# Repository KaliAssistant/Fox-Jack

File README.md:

# Fox-Jack
> Portable social-engineering LAN tool for automated payloads and wired audits — based on Luckfox Pico Max

## About

**Fox-Jack** is a low-cost, DIY social engineering LAN implant inspired by the Hak5 SharkJack.  
Designed for payload delivery, opportunistic wired auditing, and SE engagements, it features DIP-switch mode control, RGB LED feedback, and USB gadget interfaces — all powered by the **Luckfox Pico Max (RV1106G3)**.

### Features

* USB gadget function: **RNDIS** over USB
* 100 Mbps onboard **GMAC** Ethernet
* Based on **Luckfox Pico Max (RV1106G3)**
* Optional **open-source extension board PCB**:

  * 300mAh LiPo battery support (\~1–2hr uptime, longer with bigger battery)
  * **NeoPixel RGB LED** status indicator
  * **2-position DIP switch** to select payloads
* Optional **3D printable cases**
* Rootfs: **Buildroot**
* Boot: **SD card**
* U-Boot: **Luckfox official SDK**

---

## Repository Contents

* 🧰 **Luckfox Pico Official SDK**
* 🔨 **Image build scripts**
* 🧱 **3D-printable case designs**
* 🗒 **Optional extension board**:

  * KiCad project
  * Gerber files
  * BOM

---

## Parts List

| Item                                       | Qty | Link |
| ------------------------------------------ | --- | ---- |
| Luckfox Pico MAX (256 MB RAM version only) | 1   | [Amazon](https://a.co/d/7qTUaEF) |
| M2x0.4 Heat-Set Thread Insert (D3×H2.5)    | 2   | [Amazon](https://a.co/d/6mJeA5C) |
| M2x0.4 Heat-Set Thread Insert (D3×H2)      | 2   | [Amazon](https://a.co/d/6mJeA5C) |
| M2x0.4 Ultra-Low Head Torx Screws (3mm)    | 2   | [Amazon](https://a.co/d/fiHYJ7t) |
| M2x0.4 Hex Socket Head Cap Screws (10mm)   | 2   | [Amazon](https://a.co/d/4TCJOGo) |
| DIP Switch 1 Positions                     | 1   | [Amazon](https://a.co/d/8rEHPwg) |
| 302040 Lipo 3.7v battery                   | 1   | [Amazon](https://amzn.eu/d/auT4PZT) |

> [!NOTE]
> 🔧 PCB & BOM: all files in the `pcb/` directory

---

## Required Tools

* 28 AWG electrical wire
* Soldering tools:

  * Solder
  * Solder iron
  * Solder paste
  * Solder flux
  * Hot air gun (for SMD components on extension board)

---

## Fox-Jack EXT Board

#### Assembly Notes: [README](./pcb/README.md)

---

## 3D printable cases

#### see: [README](./3dp/README.md)

---

## Build Instructions

1. Create a Debian/Ubuntu/Kali (or other Debian-based) Linux environment
   *(You can use a VM or physical machine — author uses a Debian laptop)*

2. Install required dependencies:

   ```bash
   sudo ./dep.sh
   sudo apt update
   sudo apt install -y docker.io kconfig-frontends make cmake automake autoconf libtool libtool-bin rsync
   ```
   
3. Clone the repository:

   ```bash
   git clone https://github.com/KaliAssistant/Fox-Jack.git
   ```

4. Navigate into the repo:

   ```bash
   cd Fox-Jack
   ```

5. Run the build script:

   ```bash
   sudo ./build.sh all
   ```

   You will see the SDK's *lunch menu*:

   ```
   You're building on Linux
   Lunch menu...pick the Luckfox Pico hardware version:
   [4] RV1106_Luckfox_Pico_Pro_Max
   ...
   Which would you like? [default: 0]: 4

   Lunch menu...pick the boot medium:
   [0] SD_CARD
   Which would you like? [default: 0]: 0

   Lunch menu...pick the system version:
   [0] Buildroot
   Which would you like? [default: 0]: 0
   ```

> [!NOTE]
> ✅ Just enter `4 / 0 / 0` — **only Luckfox Pico Max** is supported currently.

---

## Config Options

You can tweak build options using the following:

* **Buildroot menuconfig**:

  ```bash
  sudo ./build.sh luckfox buildrootconfig
  ```

* **Kernel menuconfig**:

  ```bash
  sudo ./build.sh luckfox kernelconfig
  ```

* **Foxjack extra config (e.g., SSH key, services)**:

  ```bash
  sudo ./build.sh foxjackconfig
  ```

> [!NOTE]
> **Security Note:**
> Default root password is `foxjack`, but **SSH password login is disabled** (`PermitRootLogin prohibit-password`) for security.
> Add your public key via `foxjackconfig`.
> If you need password login, modify `/etc/ssh/sshd_config` in rootfs manually.

To access via **USB RNDIS**, make sure your host PC has a static IP in the same subnet as defined in `foxjackconfig`.

---

## Flashing to SD Card

Once the build is complete, flash the image:

```bash
sudo ./build.sh sdflash
```

You'll see:

```
WARNING: Check the SD card dev path! blkenvflash can overwrite your system drives!
Enter your SD card dev path (/dev/sxx)... >
```

> [!WARNING]
> **Be careful!** Enter the correct SD card device path to avoid overwriting your OS drive.

---

## Run Modes (Payload Selection)

Fox-Jack supports 4 modes, selected via a 2-position DIP switch:

| Mode      | SW1 | SW2 | Description    |
| --------- | --- | --- | -------------- |
| 0 (debug) | 0   | 0   | Dev/debug mode |
| 1         | 1   | 0   | Payload 1      |
| 2         | 0   | 1   | Payload 2      |
| 3         | 1   | 1   | Payload 3      |

Read via GPIO:

```c
#define SW1_PIN 67  // gpio2_a3_d (pin 27)
#define SW2_PIN 66  // gpio2_a2_d (pin 26)
```

---

### Debug Mode Details

In **debug mode** (SW1=0, SW2=0):

* USB gadget provides **RNDIS Ethernet** **+ Mass Storage**
* Payloads can be edited directly from host PC
* **LOOT** (results, passwords, hashes) is saved in:

  ```
  <UMS>/loot/
  ```

---

## Payload Examples

#### see [README](./payload_examples/README.md)

Payload filenames must follow this format:

```
E????-name.payload
```

* `E????` is a 4-digit payload ID (e.g., `E0000`)
* `name` is a short, descriptive label

**Example:**

```
E0000-arp-scan.payload
```

---

## Disclaimer

**Fox-Jack** is intended for authorized security testing, educational, and research purposes only.  
Use of this device without explicit permission on networks or systems you do not own or have authorization to test is illegal and unethical.  
The author and contributors are not responsible for any misuse or damage caused by this tool.  
Please ensure you comply with all applicable laws and obtain proper consent before deployment.

---

## License

Fox-Jack is open-source and released under the **GNU General Public License v3.0 (GPLv3)**.
You are free to use, modify, and redistribute under the terms of this license.

See the [`LICENSE`](./LICENSE) file for full details.

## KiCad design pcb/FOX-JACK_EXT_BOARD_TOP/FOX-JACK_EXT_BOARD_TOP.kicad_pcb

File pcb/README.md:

# FOX-JACK\_EXT\_BOARD

This directory contains the open-source **extension board** for the [Fox-Jack](https://github.com/KaliAssistant/Fox-Jack) project.

Designed with a **stacked PCB layout** inspired by modular smartphones (like iPhones), the board achieves a **compact**, **robust**, and **DIY-friendly** assembly with the **Luckfox Pico Max**.

---

## Board Structure

The extension board is made up of **two stacked PCBs**:

### 1. `FOX-JACK_EXT_BOARD_TOP`

* Primary functional PCB
* PCB thickness: **0.8mm**
* Hosts core components: battery management, WS2812 (NeoPixel), DIP switch, etc.

### 2. `FOX-JACK_EXT_BOARD_MID`

* Acts as a **mechanical connector** and **base shim**
* PCB thickness: **1.6mm**
* Designed to fit perfectly between the `TOP` board and the **Luckfox Pico Max**
* Provides mechanical rigidity and solder alignment

> [!NOTE]
>  This stacked layout allows professional-looking compact integration at minimal cost and effort.

---

## Assembly Notes

> [!NOTE]
> Soldering requires careful thermal profiling!

* **Top Board (`TOP`)**

  * Use **high-temperature solder paste** (e.g., Sn63/Pb37 or SAC305)

* **Mid Board (`MID`)**

  * Use **low-temperature solder paste** (e.g., Sn42/Bi58) for the mechanical + electrical bridge with the Pico board
  * Helps avoid reflowing the `TOP` board during final reflow

---

## Battery Info

* Recommended: **Li-ion 3.7V 300mAh**
* Model: **302040**
* Chosen to fit snugly inside the 3D-printed case in this repo

---

## ADC Voltage Measurement

If you want to **read battery voltage** using the **Pico’s ADC**:

* Remove **R57** on the **Luckfox Pico Max PCB**
* (R57 is a **10K ±5% pull-up** resistor that affects accurate voltage reading)
* See https://github.com/LuckfoxTECH/luckfox-pico/issues/174

---

## Compatibility with 3D-Printed Case

To fit the extension + Pico board into the provided **3D-printed case**, perform the following hardware mods:

1. **Remove** the following components from the Pico:

   * **RJ45 Ethernet socket**
   * **CSI Camera connector**
   * **RTC battery holder**

2. **Modify Ethernet Cable**:

   * Cut and strip a short **4P (or 8P)** RJ45 cable
   * Remove filler and outer jacket
   * Solder directly to the Pico’s Ethernet pads
   * 4P is enough for **100 Mbps** **(rv1106g3 gmac only support 100Mbps phy)**

---

## Files Included

* ✅ KiCad project files (`.kicad_pcb`, `.sch`, etc.)
* ✅ Gerber + drill files (for fabrication)
* ✅ BOM (Bill of Materials)
* ✅ Assembly guidelines
* ✅ 3D models and printable case (`.stl`, in [<repo_dir>/3dp](../3dp/))

---

## PCB Manufacturing Notes (e.g., JLCPCB)

When ordering:

* ✅ Use **standard PCB processing** (no special options)
* ❗️ **Do NOT enable “Castellated Holes”** — leave this option **unchecked**
* ✅ This keeps the board cost around **\$4 USD**
* ❌ Enabling Castellated Holes may raise the quote to **\$40+ USD**, unnecessarily

> [!NOTE]
> This design **does not use true castellated holes**.
> Instead, it relies on **DIY-style side solder bridging** using exposed edge pads on a regular PCB.
> This approach is **cost-efficient**, **strong enough**, and perfectly suited for **DIY assembly** — no need for expensive edge plating.

---

## License

Licensed under **GNU GPLv3**.
Feel free to **use**, **study**, **modify**, and **share** under the same license.

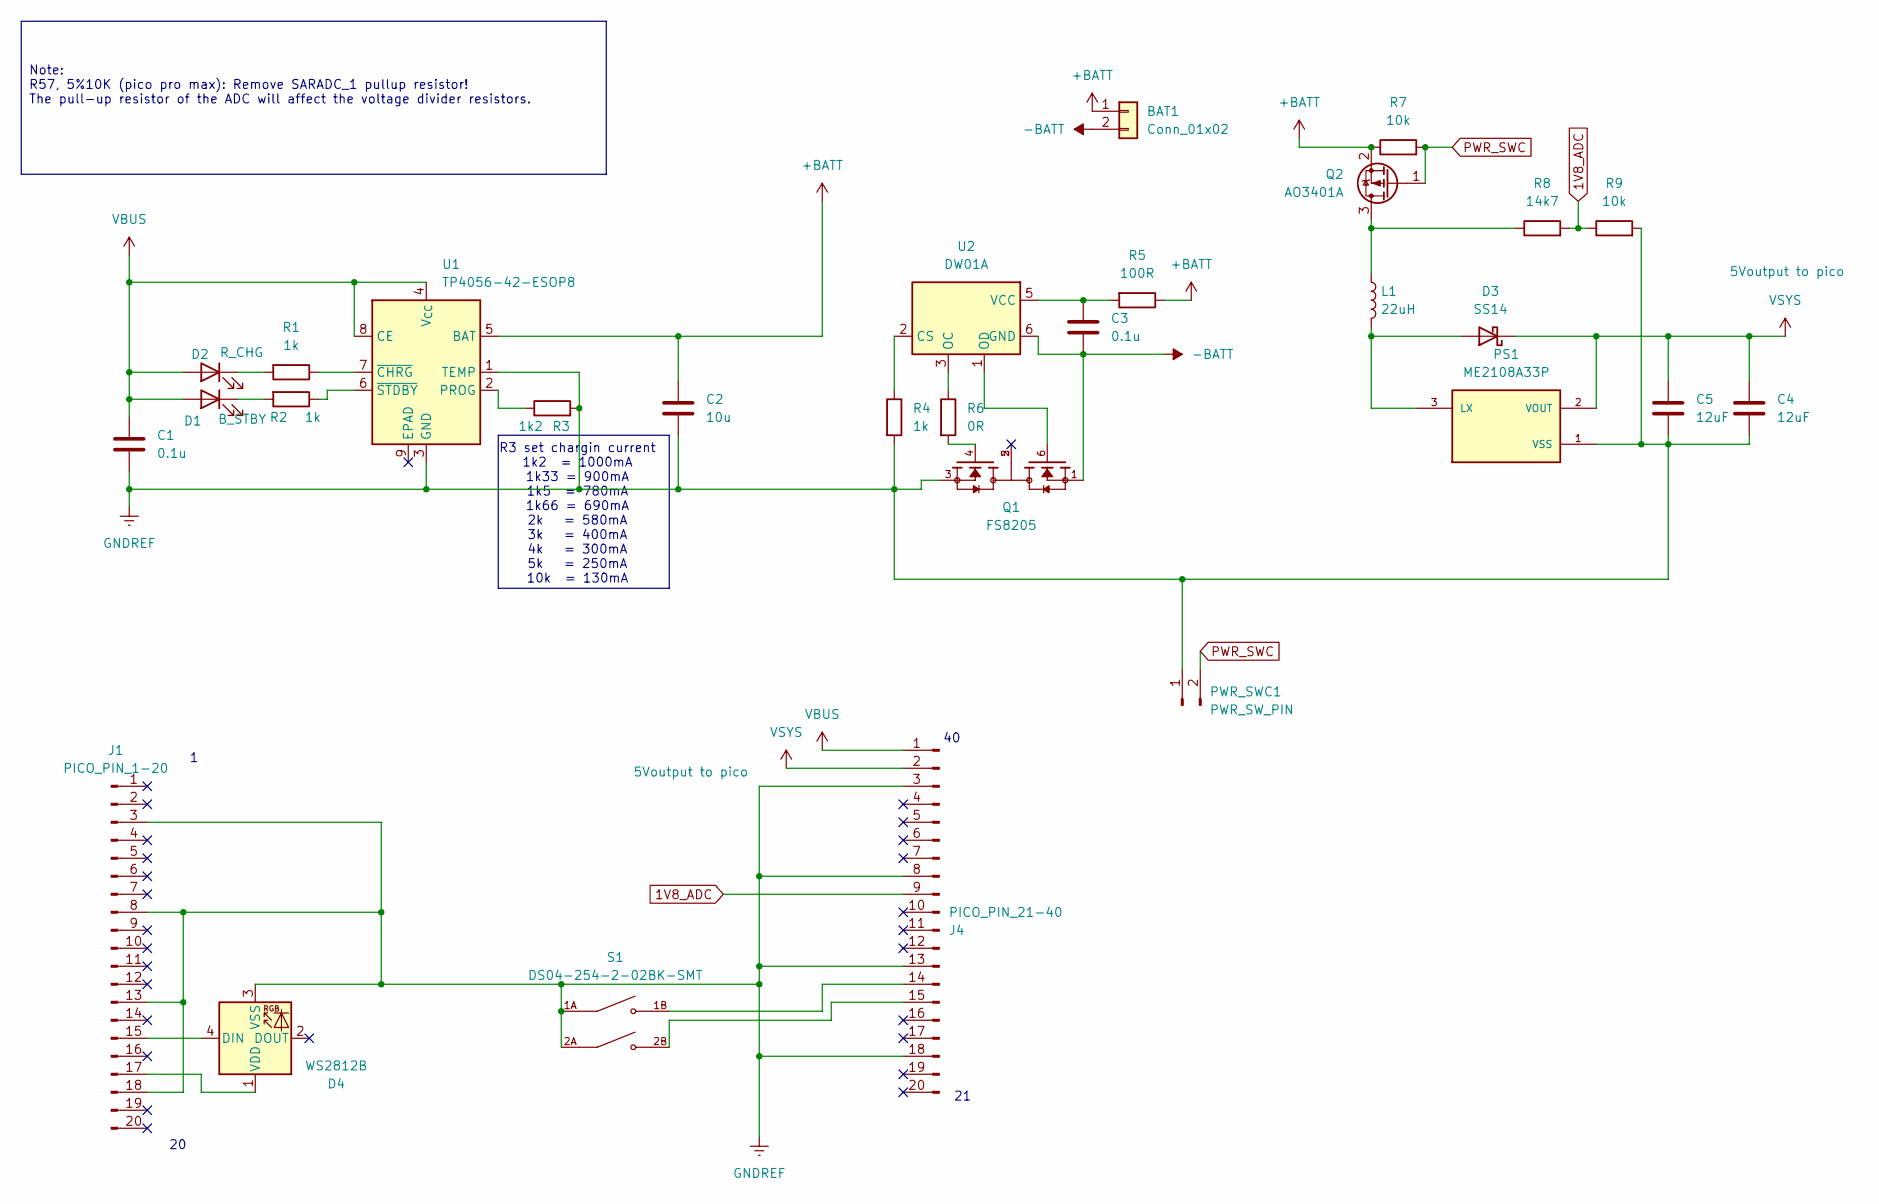
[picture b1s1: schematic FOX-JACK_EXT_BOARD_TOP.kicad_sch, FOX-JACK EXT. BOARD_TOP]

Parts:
BAT1: Conn_01x02; BAT_PAD
C1, C3: 0.1u; C_0402_1005Metric
C2: 10u; C_0603_1608Metric
C4, C5: 12uF; C_1210_3225Metric
D1: B_STBY; LED_0603_1608Metric
D2: R_CHG; LED_0603_1608Metric
D3: SS14; D_SMA
D4: WS2812B; LED_WS2812B_PLCC4_5.0x5.0mm_P3.2mm
J1: PICO_PIN_1-20; PinHeader_1x20_P2.54mm_Vertical
J4: PICO_PIN_21-40; PinHeader_1x20_P2.54mm_Vertical
L1: 22uH; L_Changjiang_FNR3015S
PS1: ME2108A33P; CONV_ME2108A33P; PARTREV V10.0
PWR_SWC1: PWR_SW_PIN; PinHeader_1x02_P2.54mm_Vertical
Q1: FS8205; SOT95P280X145-6N; PARTREV 1.9
Q2: AO3401A; SOT-23
R1, R2: 1k; R_0402_1005Metric
R3: 1k2; LED_0402_1005Metric
R4: 1k; R_0603_1608Metric
R5: 100R; R_0805_2012Metric
R6: 0R; LED_0805_2012Metric
R7, R9: 10k; R_0402_1005Metric
R8: 14k7; R_0402_1005Metric
S1: DS04-254-2-02BK-SMT; SW_DS04-254-2-02BK-SMT; PARTREV V0.0
U1: TP4056-42-ESOP8; SOIC-8-1EP_3.9x4.9mm_P1.27mm_EP2.41x3.3mm_ThermalVias
U2: DW01A; SOT-23-6

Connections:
1V8_ADC: J4.9, R8.2, R9.1
+BATT: BAT1.1, C2.1, Q2.2 (S), R5.1, R7.1, U1.5 (BAT)
-BATT: BAT1.2, C3.2, Q1.1, U2.6 (GND)
GNDREF: C1.2, C2.2, C4.2, C5.2, D4.3 (VSS), J1.3, J1.8, J1.13, J1.18, J4.3, J4.8, J4.13, J4.18, PS1.1 (VSS), PWR_SWC1.1, Q1.3, R3.2, R4.2, R9.2, S1.1A, S1.2A, U1.1 (TEMP), U1.3 (GND)
unnamed: D1.1 (K), R2.2
unnamed: D2.1 (K), R1.2
unnamed: D3.2 (A), L1.2, PS1.3 (LX)
unnamed: D4.4 (DIN), J1.15
unnamed: D4.1 (VDD), J1.17
unnamed: J4.14, S1.1B
unnamed: J4.15, S1.2B
unnamed: Q1.4, R6.2
unnamed: L1.1, Q2.3 (D), R8.1
unnamed: R3.1, U1.2 (PROG)
unnamed: R1.1, U1.7 (~CHRG)
unnamed: R2.1, U1.6 (~STDBY)
unnamed: R4.1, U2.2 (CS)
unnamed: R6.1, U2.3 (OC)
unnamed: Q1.6, U2.1 (OD)
unnamed: C3.1, R5.2, U2.5 (VCC)
PWR_SWC: PWR_SWC1.2, Q2.1 (G), R7.2
VBUS: C1.1, D1.2 (A), D2.2 (A), J4.1, U1.4 (V_{CC}), U1.8 (CE)
VSYS: C4.1, C5.1, D3.1 (K), J4.2, PS1.2 (VOUT)

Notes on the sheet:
R3 set chargin current 1k2 = 1000mA 1k33 = 900mA 1k5 = 780mA 1k66 = 690mA 2k = 580mA 3k = 400mA 4k = 300mA 5k = 250mA 10k = 130mA
Note: R57, 5%10K (pico pro max): Remove SARADC_1 pullup resistor! The pull-up resistor of the ADC will affect the voltage divider resistors.

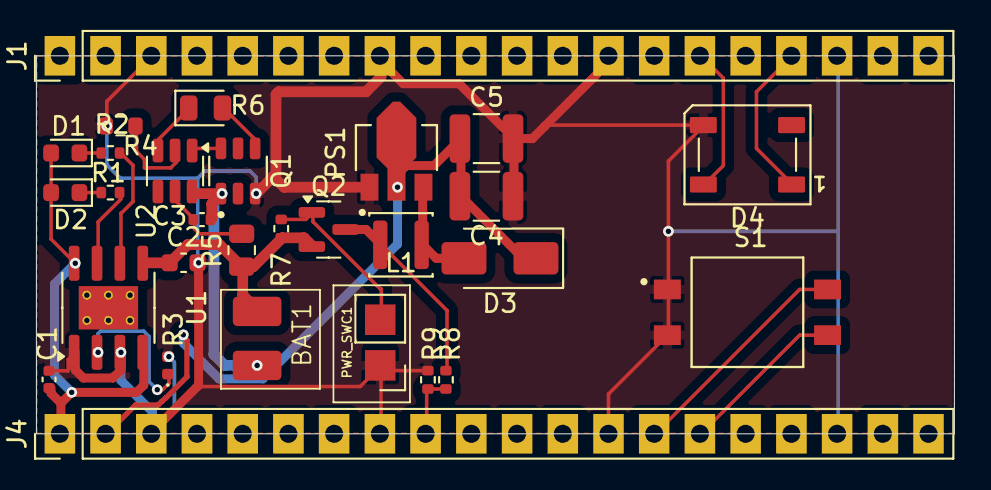
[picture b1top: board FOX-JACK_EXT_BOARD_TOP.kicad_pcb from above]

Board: 2 copper layers, 51.0 x 21.0 mm, 29 parts (0 on the bottom side), 23 nets.

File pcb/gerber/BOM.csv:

Index,LCSC#,MPN,Manufacturer,Package,Customer #,Description,RoHS,Quantity,MOQ,Multiple,Unit Price($),Extended Price($),Product Link
1,C236798,ME2108A50PG,MICRONE,SOT-89-3,PS1,Boost 5V 400mA 900mV~6.5V SOT-89-3 DC-DC Converters ROHS,yes,5,5,5,0.0680,0.34,https://lcsc.com/product-detail/dc-dc-converters_microne-me2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
2,C21190,0603WAF1001T5E,UNI-ROYAL,0603,R4,100mW Thick Film Resistor 75V ±100ppm/℃ ±1% 1kΩ 0603 Chip Resistor - Surface Mount ROHS,yes,100,100,100,0.0011,0.11,https://lcsc.com/product-detail/chip-resistor-surface-mount_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
3,C83852,SS14,onsemi,SMA(DO-214AC),D3,40V 500mV@1A 1A SMA(DO-214AC) Schottky Diodes ROHS,yes,5,5,5,0.1319,0.66,https://lcsc.com/product-detail/schottky-diodes_onsemi-ss14_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
4,C281774,RT0402BRD0714K7L,YAGEO,0402,R8,62.5mW Thin Film Resistor 50V ±25ppm/℃ ±0.1% 14.7kΩ 0402 Chip Resistor - Surface Mount ROHS,yes,50,50,50,0.0195,0.98,https://lcsc.com/product-detail/chip-resistor-surface-mount_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
5,C15127,AO3401A,AOS,SOT-23,Q2,"30V 85mΩ@2.5V,2.5A 1.3V@250uA 1 P-Channel SOT-23 MOSFETs ROHS",yes,10,10,10,0.0602,0.60,https://lcsc.com/product-detail/mosfets_aos-ao3401a_C15127.html
6,C19702,CL10A106KP8NNNC,Samsung Electro-Mechanics,0603,C2,10V 10uF X5R ±10% 0603 Multilayer Ceramic Capacitors MLCC - SMD/SMT ROHS,yes,20,20,20,0.0058,0.12,https://lcsc.com/product-detail/multilayer-ceramic-capacitor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
7,C60490,RC0402FR-0710KL,YAGEO,0402,"R7,R9",62.5mW Thick Film Resistor 50V ±100ppm/℃ ±1% 10kΩ 0402 Chip Resistor - Surface Mount ROHS,yes,100,100,100,0.0006,0.06,https://lcsc.com/product-detail/chip-resistor-surface-mount_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
8,C17477,0805W8F0000T5E,UNI-ROYAL,0805,R6,125mW Thick Film Resistor 150V ±800ppm/℃ ±1% 0Ω 0805 Chip Resistor - Surface Mount ROHS,yes,100,100,100,0.0017,0.17,https://lcsc.com/product-detail/chip-resistor-surface-mount_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
9,C2843785,XL-5050RGBC-WS2812B,XINGLIGHT,SMD5050,D4,SMD5050 RGB LEDs(Built-in IC) ROHS,yes,10,10,10,0.0490,0.49,https://lcsc.com/product-detail/rgb-leds-built-in-ic_xinglig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
10,C167761,FNR3015S220MT,cjiang (Changjiang Microelectronics Tech),"SMD,3x3mm",L1,"690mA 22uH Magnetic Shielded Inductor ±20% 680mA SMD,3x3mm Power Inductors ROHS",yes,20,20,20,0.0735,1.47,https://lcsc.com/product-detail/power-inductors_cjiang-chang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
11,C6331180,2.54-2P TPGT,SHOU HAN,SMD,S1,"2 SPST 24V Black 25mA 3,000 Cycles Slide, Rocked SMD DIP Switches ROHS",yes,1,1,1,0.4163,0.42,https://lcsc.com/product-detail/dip-switches_shou-han-2-54-2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
12,C60474,CC0402KRX7R7BB104,YAGEO,0402,"C1,C3",16V 100nF X7R ±10% 0402 Multilayer Ceramic Capacitors MLCC - SMD/SMT ROHS,yes,100,100,100,0.0009,0.09,https://lcsc.com/product-detail/multilayer-ceramic-capacitor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
13,C965799,XL-1608SURC-06,XINGLIGHT,0603,D2,20mA 225mcd Water Clear op View Mount 620nm~630nm Red 120° 50mW 2.3V 0603 LED Indication - Discrete ROHS,yes,100,100,100,0.0032,0.32,https://lcsc.com/product-detail/led-indication-discrete_xing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
14,C138687,CL32B106KBJNNNE,Samsung Electro-Mechanics,1210,"C4,C5",50V 10uF X7R ±10% 1210 Multilayer Ceramic Capacitors MLCC - SMD/SMT ROHS,yes,2,1,1,0.1571,0.31,https://lcsc.com/product-detail/multilayer-ceramic-capacitor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
15,C382139,TP4056,TPOWER,ESOP-8,U1,4V~6V Lithium-ion/Polymer 1 ESOP-8 Battery Management ROHS,yes,5,5,5,0.0888,0.44,https://lcsc.com/product-detail/battery-management_tpower-tp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
16,C17408,0805W8F1000T5E,UNI-ROYAL,0805,R5,125mW Thick Film Resistor 150V ±100ppm/℃ ±1% 100Ω 0805 Chip Resistor - Surface Mount ROHS,yes,100,100,100,0.0019,0.19,https://lcsc.com/product-detail/chip-resistor-surface-mount_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
17,C106235,RC0402FR-071KL,YAGEO,0402,"R1,R2",62.5mW Thick Film Resistor 50V ±100ppm/℃ ±1% 1kΩ 0402 Chip Resistor - Surface Mount ROHS,yes,100,100,100,0.0006,0.06,https://lcsc.com/product-detail/chip-resistor-surface-mount_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
18,C2927799,DW01A,YONGYUTAI,SOT-23-6,U2,1.5V~8V Lithium-ion/Polymer 1 SOT-23-6 Battery Management ROHS,yes,20,20,20,0.0247,0.49,https://lcsc.com/product-detail/battery-management_yongyutai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
19,C965807,XL-1608UBC-04,XINGLIGHT,0603,D1,20mA 300mcd Water Clear op View Mount 455nm~475nm Blue 120° 70mW 3.3V 0603 LED Indication - Discrete ROHS,yes,100,100,100,0.0035,0.35,https://lcsc.com/product-detail/led-indication-discrete_xing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
20,C2909307,FRC0402F1201TS,FOJAN,0402,R3,62.5mW Thick Film Resistor 50V ±100ppm/℃ ±1% 1.2kΩ 0402 Chip Resistor - Surface Mount ROHS,yes,100,100,100,0.0005,0.05,https://lcsc.com/product-detail/chip-resistor-surface-mount_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
21,C2830320,FS8205A,TECH PUBLIC,SOT-23-6,Q1,20V 9A 31.5mΩ@2.5V 1.5W 1.2V@250uA SOT-23-6 MOSFETs ROHS,yes,10,10,10,0.0449,0.45,https://lcsc.com/product-detail/mosfets_tech-public-fs8205a_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

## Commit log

2025-06-27 add 3dp cases
2025-07-01 add pkg
2025-07-01 add gitign
2025-07-01 upd gitign
2025-07-03 add build scripts
2025-07-03 update gitign
2025-07-04 add more func
2025-07-11 2025.05-dev
2025-07-18 new gpio ctrl
2025-07-21 add battery monitor support
2025-07-24 payloads and README
2025-07-24 update 3dp cases
2025-07-24 typo
2025-07-25 UPDATE README and add example payloads
2025-07-26 UPDATE PCB
2025-07-26 clean gitkeep
2025-07-28 MORE README AND FIX SOME BUG
2025-07-29 just for my blog only
2025-07-30 add examples to udisk img
2025-07-31 UPDATE #DP case
2025-12-11 Update Amazon link for 302040 Lipo battery
